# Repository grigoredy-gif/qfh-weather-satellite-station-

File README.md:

# QFH weather-satellite station: my own antenna and an all-discrete receiver

I'm Edy Grigore, an Electrical Engineering student at the University of
Twente. This is my personal project to receive weather satellites on 137 MHz
with hardware I designed myself: a QFH antenna and a superheterodyne receiver
built only from discrete parts (transistors, diodes, coils and capacitors, no
ICs in the signal path).

## Why I'm doing this

In my first year, the Module 4 project was to design an antenna and a
transmitter PCB. I really enjoyed that field, together with the High Frequency
Electronics, Electromagnetostatics and Electrodynamics courses, so I wanted to
go deeper: design my own antenna and my own receiver, and do the receiver fully
analog so I have to understand every stage at component level.

The NOAA satellites the receiver was designed for were switched off in 2025,
and the remaining Meteor-M satellites send a digital signal an analog FM
receiver cannot decode. So I test the antenna and the receiver separately: the
antenna with an SDR on Meteor-M, the receiver with recorded NOAA passes played
back through an ADALM-Pluto. More in the
[receiver README](fm_receiver/README.md#motivation).

## What's in here

| Folder | What it is | Status |
|---|---|---|
| [`qfh_matlab`](qfh_matlab) | MATLAB toolchain that designs the QFH antenna, exports it to NEC2 and prints a drilling template | antenna designed, simulated and built |
| [`fm_receiver`](fm_receiver) | the receiver design and its LTspice simulations, block by block up to the full chain | simulated from RF input to the ADC |
| [`pcb`](pcb) | the KiCad board for the receiver | designed and checked, ready to order |
| [`lrpt_decoder`](lrpt_decoder) | my own MATLAB analysis chain for Meteor-M LRPT recordings | working; taught me my signal was too weak |
| [`baseband_tools`](baseband_tools) | tools to check an SDR recording before decoding it | working |

## Highlights

- A superheterodyne receiver with about **130 dB** of gain: band-pass filter,
  LNA, mixer, a 25 MHz crystal oscillator multiplied ×5 to 125 MHz, a 12.9 MHz
  IF with four cascode stages, a limiter and a slope detector.
- Every block **simulated in LTspice** on its own, then connected, then the
  whole receiver from an FM input to the audio at the ADC.
- A **2-layer PCB** (180 × 75 mm, 196 parts) with the layout built around RF
  rules: an unbroken ground plane, a straight IF strip, tight tuned circuits
  and test points for block-by-block bring-up.
- The antenna toolchain reproduces its reference program **exactly** (all 127
  NEC wire cards identical) and adds a frequency correction found in simulation.

## What's next

Order and build the PCB, align it one block at a time, and feed it a recorded
satellite pass. On the reception side: an LNA and a 137 MHz SAW filter in
front of the SDR, then another try at Meteor-M.

After that, I want to close the loop with my own hardware on both ends: build
a second QFH antenna and an FM transmitter on my own PCB, and send information
between the two stations, on a frequency I'm allowed to transmit on.

## Tools

LTspice, KiCad 10, MATLAB R2025a, 4nec2 / NEC2, SatDump, an ADALM-Pluto SDR
and a miniVNA Tiny.

## Credits and license

This is my project. I used Claude (Anthropic) as an AI assistant along the
way; each folder's README says exactly what it helped with. The antenna code
is a MATLAB port of John Coppens' online QFH calculator and of QFH2nec, both
GPL-licensed, so `qfh_matlab` is GPL-3.0. Everything else is MIT licensed
(see [LICENSE](LICENSE)).

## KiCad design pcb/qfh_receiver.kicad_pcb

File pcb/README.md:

# PCB — discrete 137.9 MHz FM satellite receiver

This is the circuit board for the receiver I simulated in
[`../fm_receiver`](../fm_receiver). The board is built from that simulation:
its schematic was generated from the full-receiver netlist `sim12`, and if the
board and that netlist ever disagree, the netlist wins.

## The board at a glance

| | |
|---|---|
| Size | 180 × 75 mm, 2 layers, FR4 1.6 mm |
| Parts | 196, all on the top side |
| Bottom layer | one ground plane |
| Controller | ESP32-DevKitC V4 on a socket (its ADC digitizes the audio) |
| Supply | the DevKitC's 5V pin (really about 4.6 V), about 41 mA |
| Checks | KiCad DRC clean at a 0.254 mm clearance floor; schematic and board match pad for pad |

## Floorplan

```
+--------------------------------------------------------------------------+
| [SMA ant] BPF (2 air coils, | LNA | MIXER | == IF STRIP, 96 dB, straight |
|  plane cutouts) [SMA test]  | SMD | +T1   |  T2 [1][2][3][4] lim | DET T7 |
|-------- via wall ----------------------------------------------- via wall|
| LO CHAIN: xtal 25MHz | buffer | x5 (2 air coils) -> up into mixer LO port |
|                      AUDIO chain (2400 Hz, folds freely) <- from detector |
|  power entry / bulk filter          ESP32 module socket [USB over edge] > |
+--------------------------------------------------------------------------+
```

The weakest signals (microvolts) start at the left edge and the strongest
(volts) end at the right. The IF strip runs in a straight line with its input
and output at opposite ends, because with 96 dB of gain even a little coupling
from the output back to the input would make it oscillate.

## Layout rules I followed

- **The bottom layer is ground.** Everything is routed on top. A few short
  bottom-layer hops were unavoidable where a trace had to cross another; each
  one is listed and justified in the design log.
- **Shielding provisions for free.** Rows of ground vias between the IF stages
  and between the RF and the LO/audio sections, with exposed ground strips so a
  brass shield can be soldered on later if the strip oscillates.
- **Tight RF loops.** Every tuned circuit's parts sit right at its coil, and the
  LNA's emitter bypass is within about 5 mm of copper of the transistor. At VHF
  a few nanohenries of track change the tuning and the gain.
- **A real 50 ohm antenna input.** The SMA feeds the filter through a 1.5 mm
  coplanar line with ground on both sides.
- **Decoupling everywhere.** Every IF stage has its own 100 nF capacitors on its
  supply and on its cascode bias, fed through its own 10 ohm resistor, so the
  stages cannot talk to each other through the supply.
- **Test points for bring-up.** A second, unfitted SMA with a 0 ohm link at the
  filter→LNA seam (to measure the filter and the LNA separately on a VNA), an
  injection pad at the first IF stage, and a monitor pad on the audio.
- **No parts on the back and no mounting holes**, both on purpose.

The toroids (T37-6, 27 turns) and the air coils (5 mm diameter) use my own
footprints in `qfh_receiver.pretty`. The air-coil footprint keeps copper away
from under the coil, because a ground plane there would kill its Q.

## How I checked it

KiCad's design-rule check is clean at a 0.254 mm clearance floor. The
schematic was generated from the simulation netlist and compared with the board
pad by pad (418 connections, no differences). Every part value was checked
against a real catalogue part at Farnell. I also had the board reviewed by
independent AI review passes, which is how several of the issues below were
found.

## Issues found and fixed

- **Two TO-92 transistor types had base and emitter swapped** because a
  generic symbol used the wrong pin order. Lesson: check each footprint's pinout
  against the datasheet, not against the symbol library.
- **The ESP32 socket would not have powered anything.** The 5 V feed landed on
  a GPIO pin and the enable pin was grounded. I fixed it after checking the
  DevKitC pinout from several sources and every way the module could be
  plugged in.
- **The "5 V" supply is really 4.6 V**, because the DevKitC puts a Schottky
  diode after USB. I re-centred every bias divider in the simulation for 4.6 V
  instead of accepting lower gain.
- **Some specified trimmers did not exist as real parts.** Together with the
  board's own parasitics this pushed three tuned circuits to the end of their
  trimmer range. I re-split the fixed capacitor and the trimmer in each one so
  the trimmer now lands mid-range.
- **The LNA's emitter bypass capacitor was 20 mm from the transistor.** That
  is about 12 nH, which would have cost 4–5 dB of gain. It is now within 5 mm.

## Bring-up plan

1. Power only: check every DC voltage against `sim12`.
2. Local oscillator: 25 MHz at the crystal, then 125 MHz at the mixer.
3. Filter and LNA: fit the test SMA, remove the 0 ohm link, sweep them on the
   VNA. Expect about 39 dB of image rejection and an LNA gain of at least
   13.5 dB.
4. IF strip: with no signal, the limiter output should show only noise (a
   steady tone means it oscillates). Then inject 12.9 MHz at the test pad and
   align the tanks.
5. The whole chain: a recorded APT pass from the Pluto into the antenna input.

Expected trimmer settings: band-pass filter about 6.5 pF, ×5 multiplier about
5.4 pF, LO output about 5.8 pF. If one lands far from that, its coil probably
came out wrong.

## Ordering

The bill of materials with Farnell order codes is `fabrication/qfh_receiver_bom.csv`, and the gerbers for JLCPCB are `fabrication/qfh_receiver_gerbers_jlc.zip`.
Every pF-range capacitor must be NP0/C0G, and the crystal must be a
fundamental-mode part. Both SMAs are edge-launch parts whose pads run to the
board edge on purpose, so the board house may ask about copper at the edge.

## Files

| File | What it is |
|---|---|
| `qfh_receiver.kicad_pro` / `.kicad_sch` / `.kicad_pcb` | the KiCad project, schematic and board |
| `qfh_receiver.kicad_dru` | custom design rules (edge clearance at the two SMAs) |
| `qfh_receiver.pretty/` | my footprints for the toroids and air coils |
| `fabrication/` | the bill of materials and the gerbers for ordering |
| `img/` | board renders |
| [`DESIGN_LOG.md`](DESIGN_LOG.md) | the complete step-by-step design log |

## Attribution

This board is my project: I set the requirements and the layout rules, and I
approved every change. I will assemble, align and measure it myself. I used
Claude (Anthropic) as an AI assistant for the KiCad work: following my
requirements and reviews, it did most of the placement and routing by script,
ran the design checks and did independent review passes. The full step-by-step
record is in [`DESIGN_LOG.md`](DESIGN_LOG.md). The motivation for the project is
in the [receiver README](../fm_receiver/README.md).

Edy Grigore

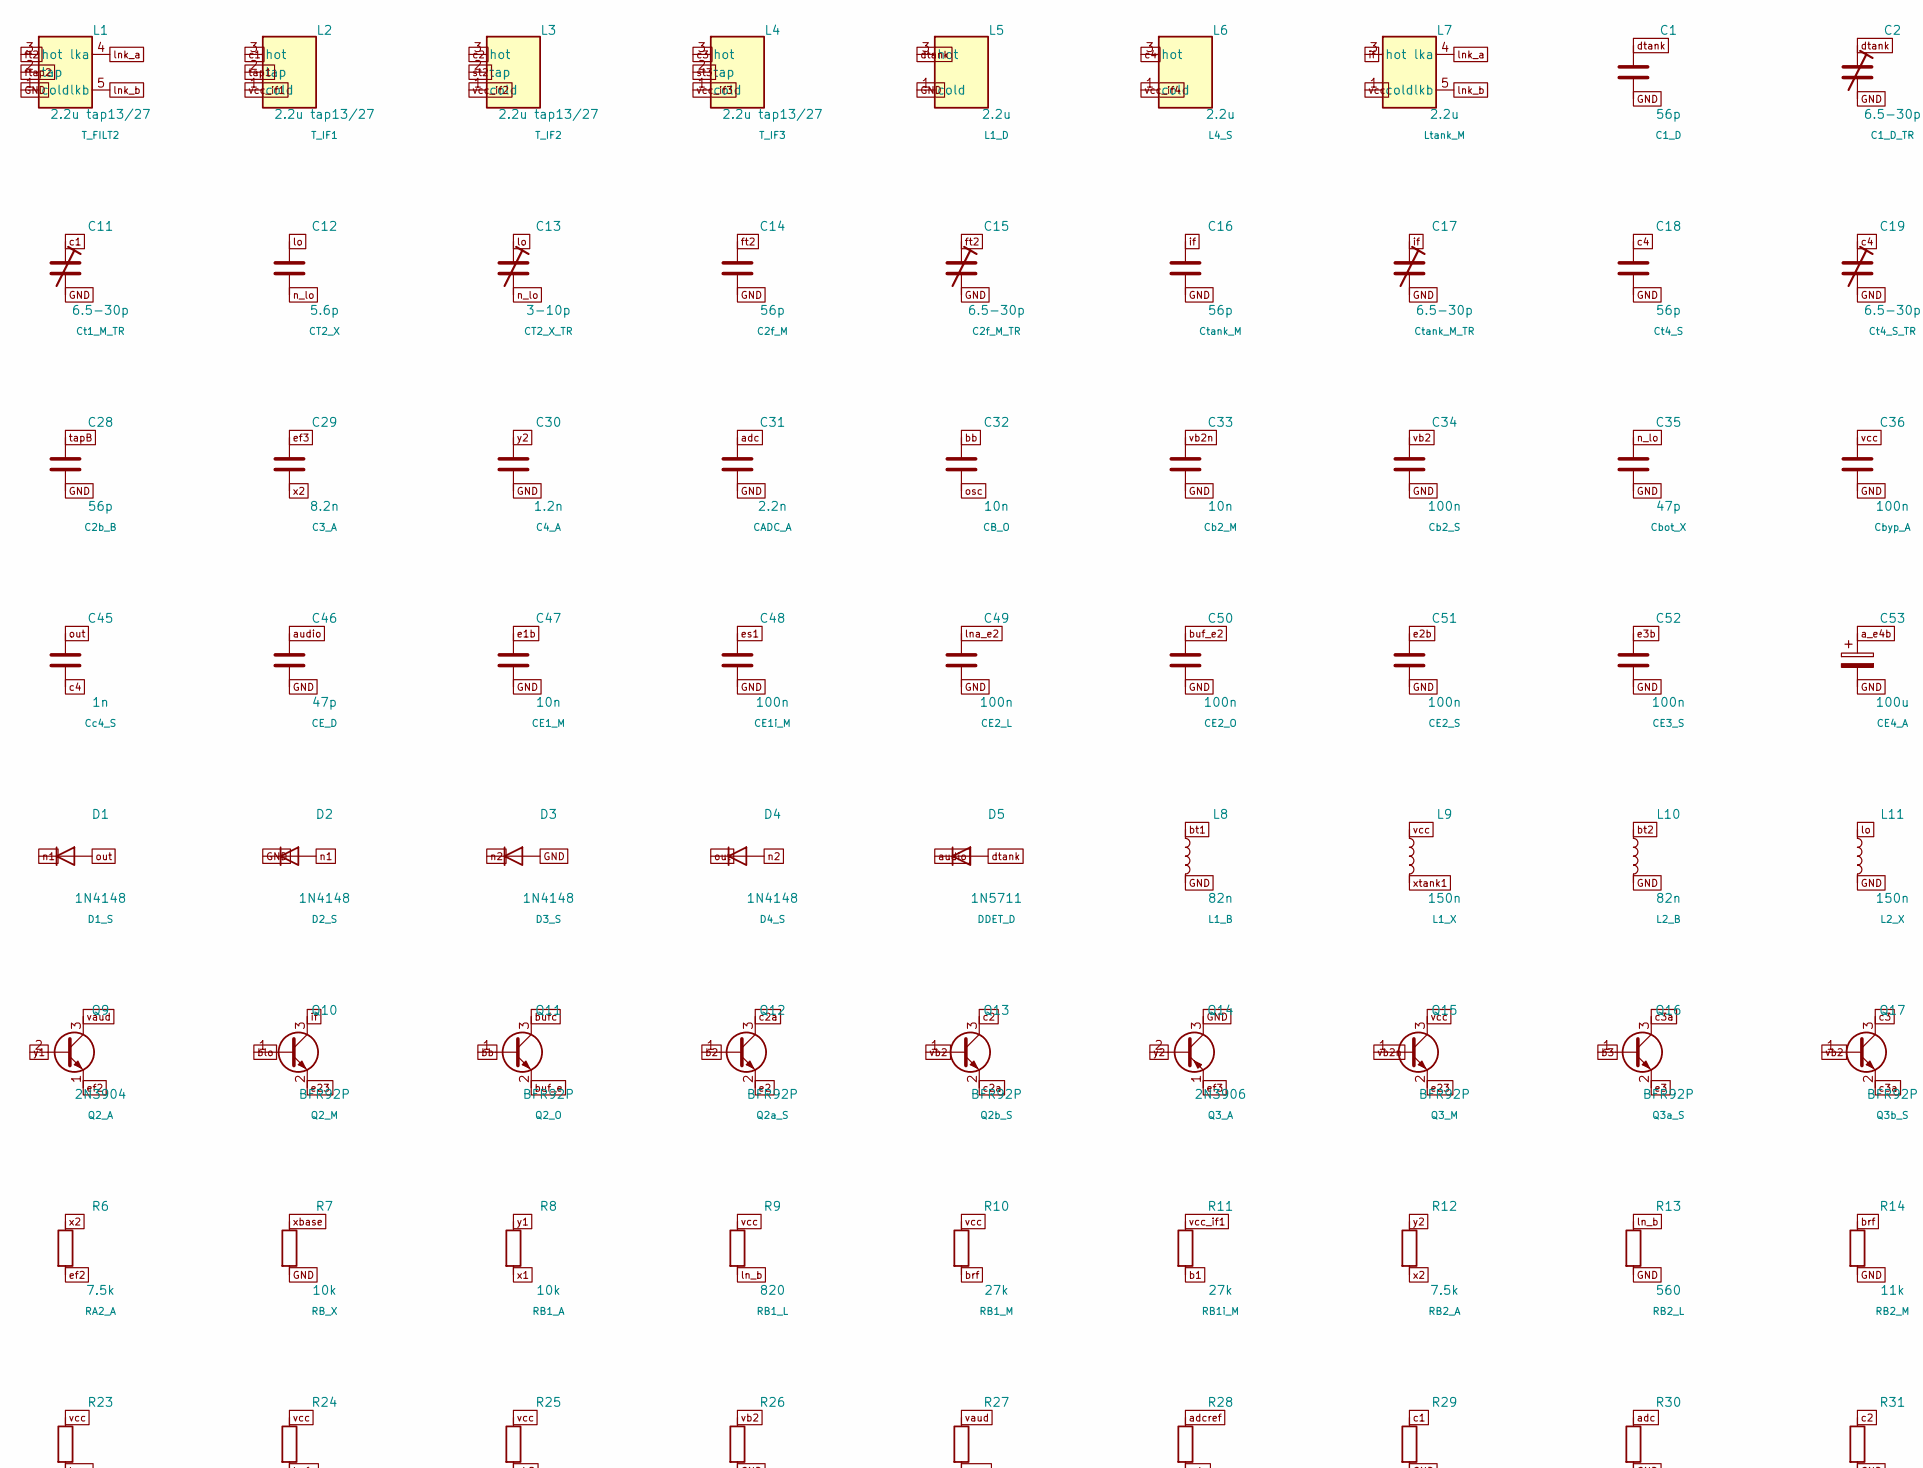
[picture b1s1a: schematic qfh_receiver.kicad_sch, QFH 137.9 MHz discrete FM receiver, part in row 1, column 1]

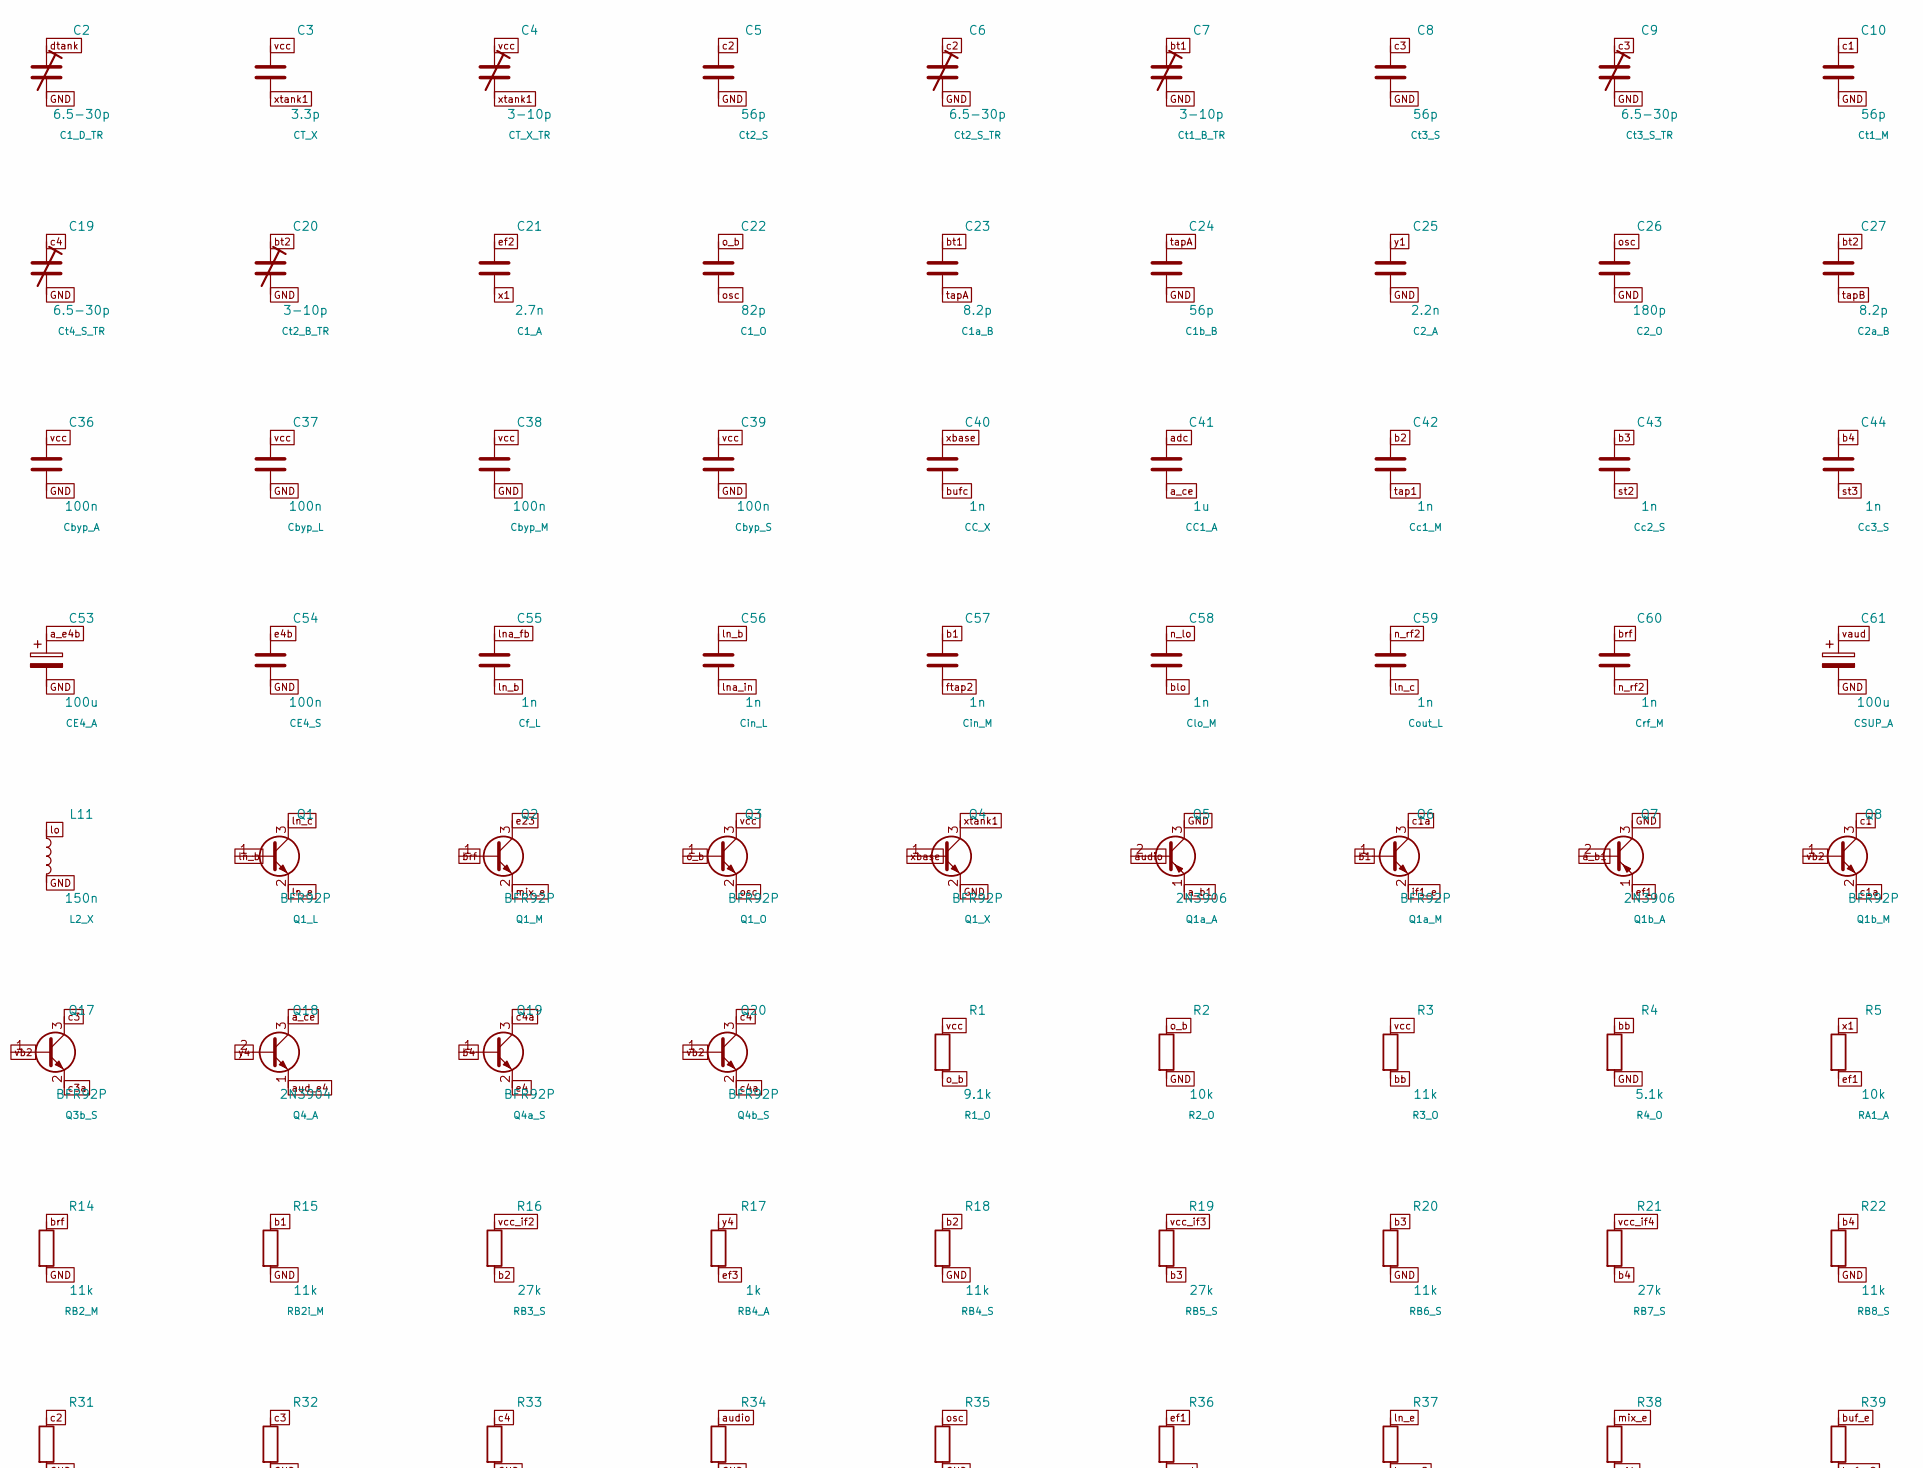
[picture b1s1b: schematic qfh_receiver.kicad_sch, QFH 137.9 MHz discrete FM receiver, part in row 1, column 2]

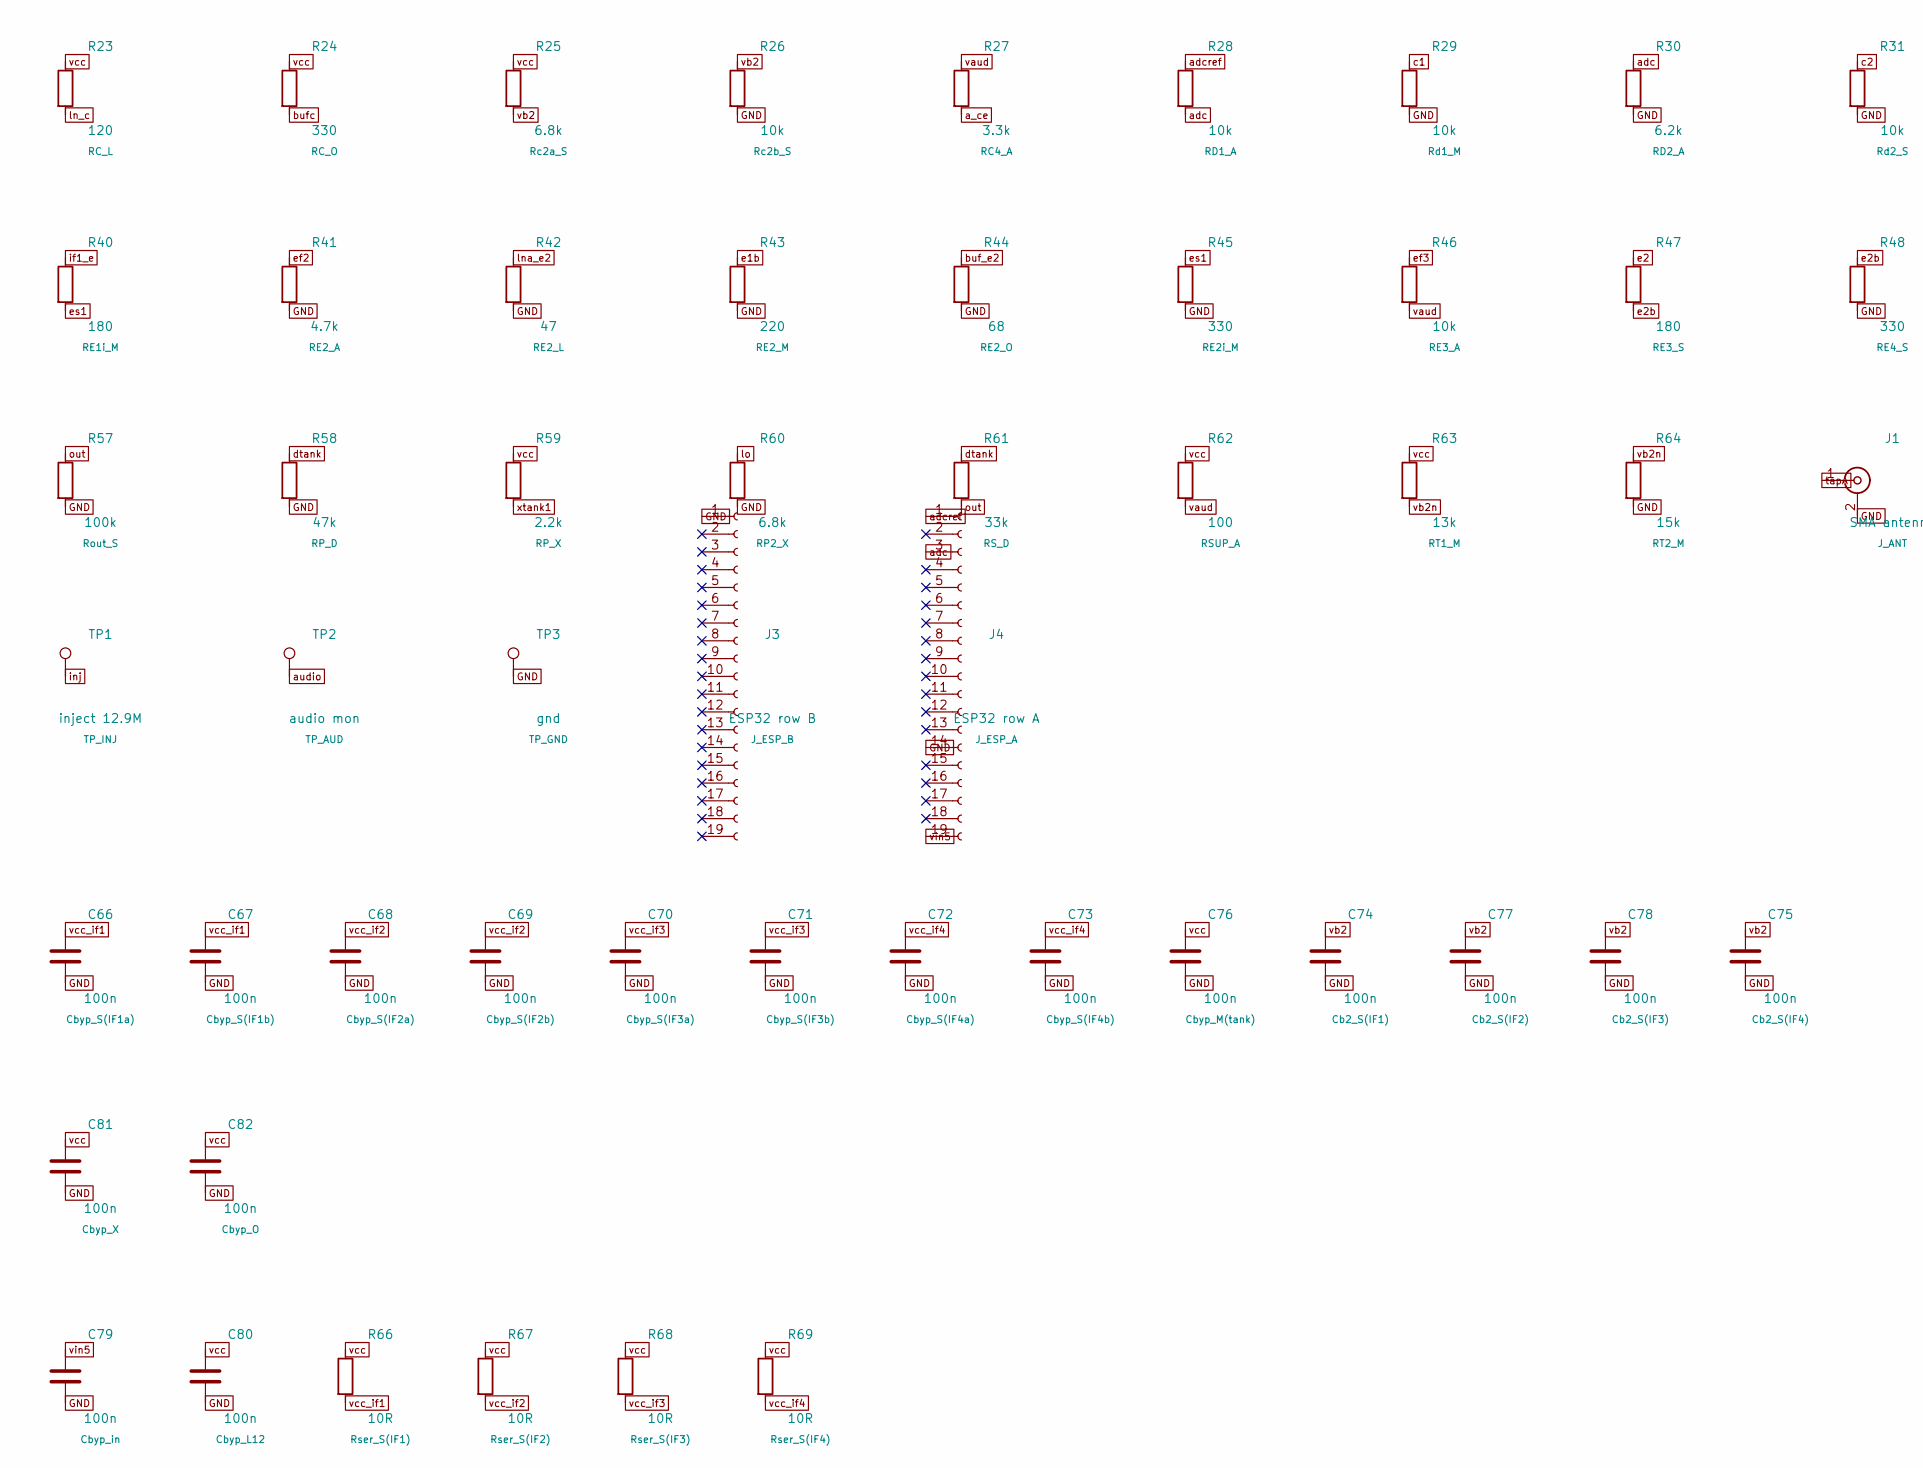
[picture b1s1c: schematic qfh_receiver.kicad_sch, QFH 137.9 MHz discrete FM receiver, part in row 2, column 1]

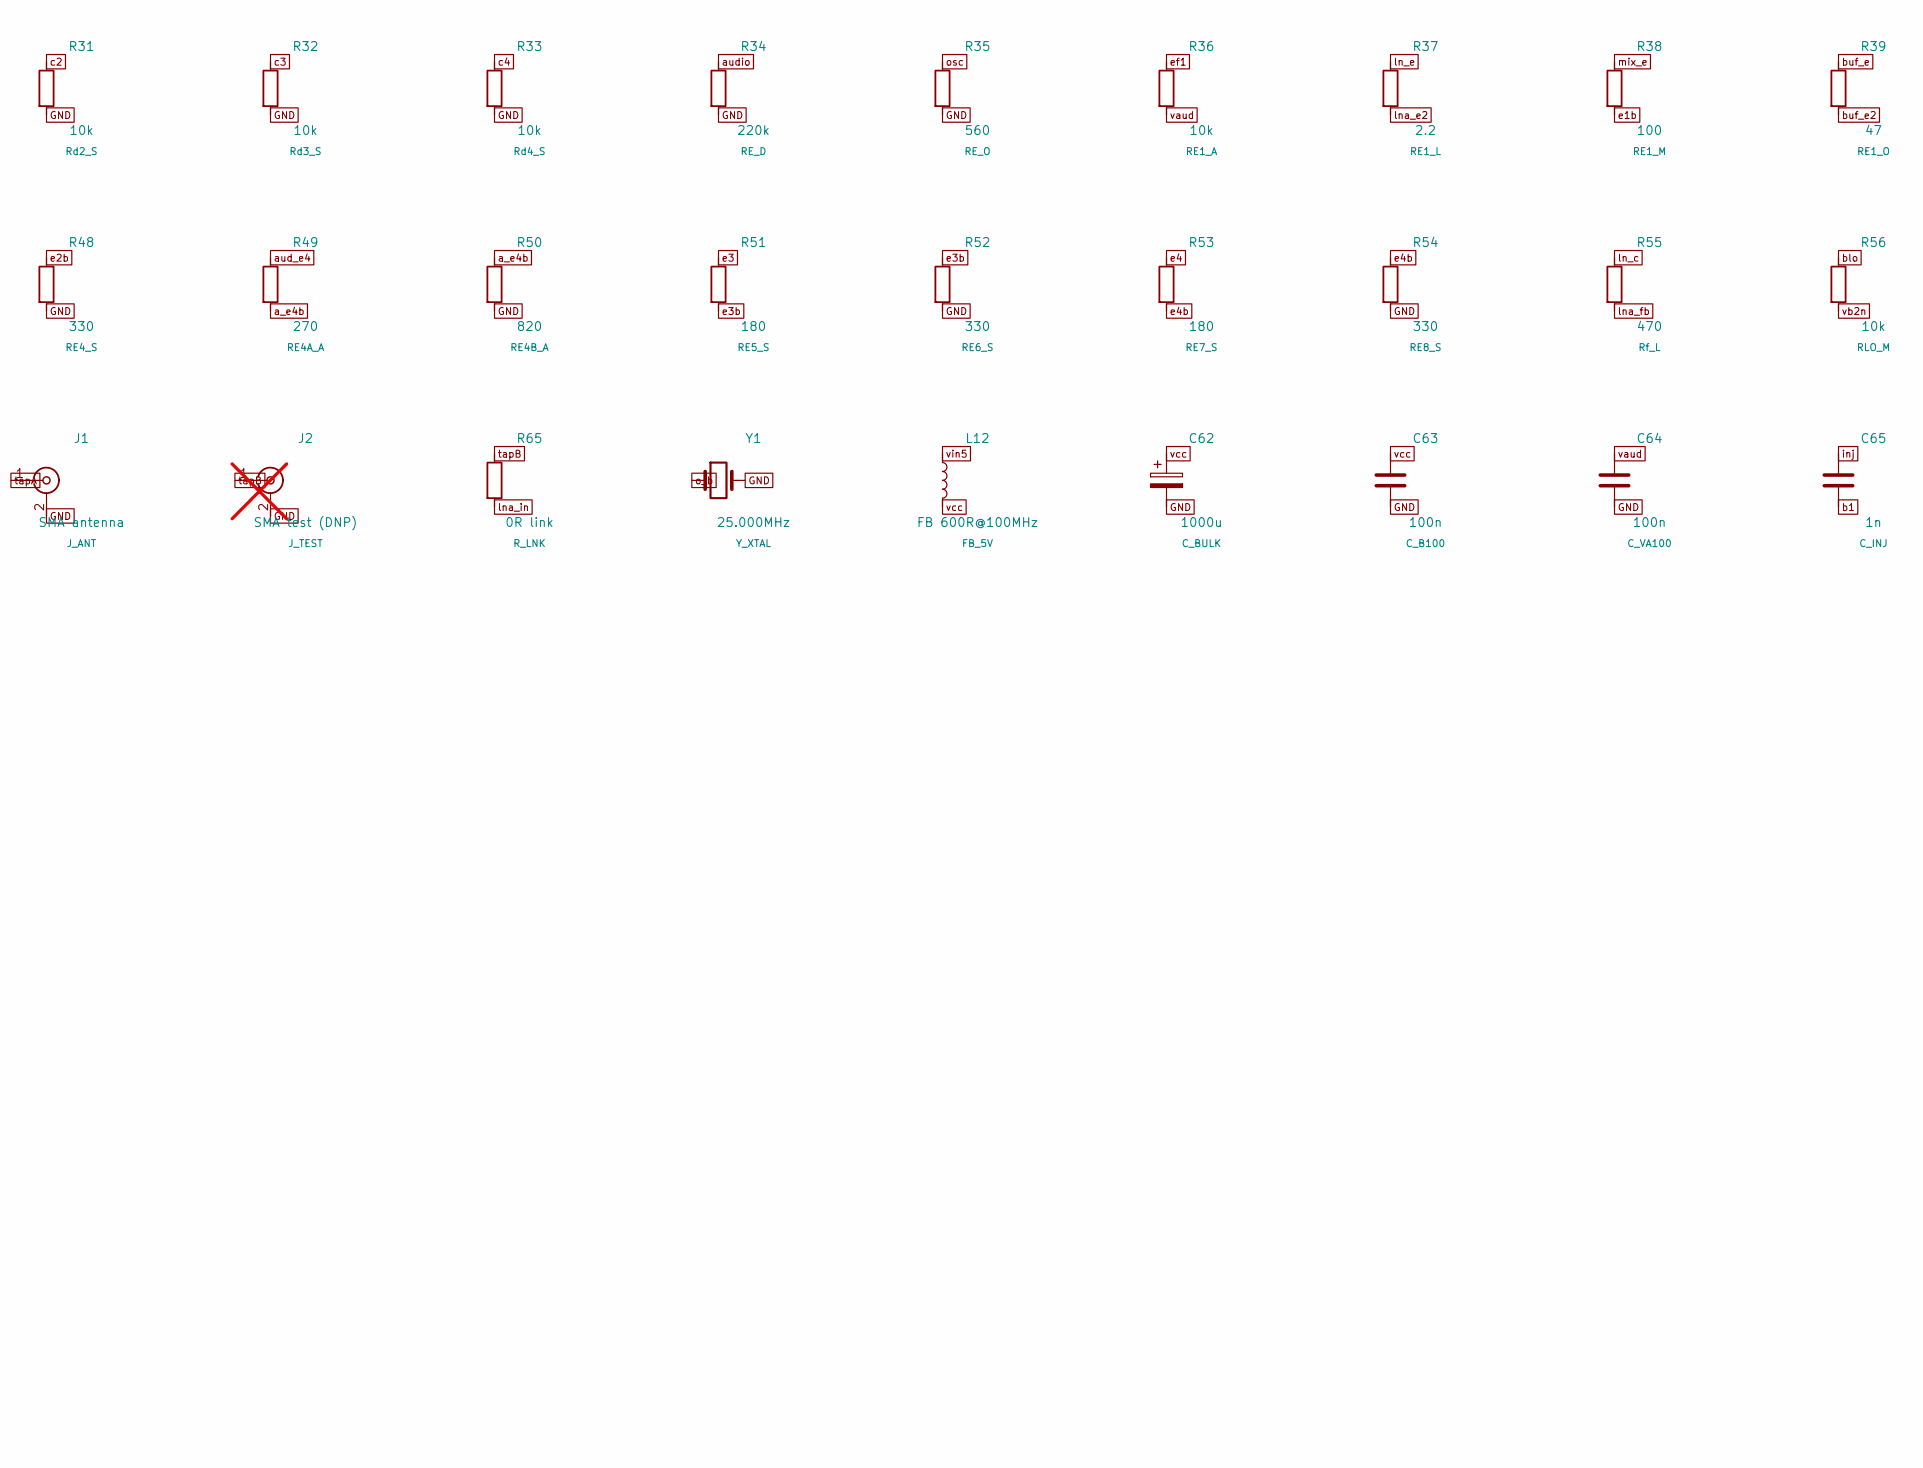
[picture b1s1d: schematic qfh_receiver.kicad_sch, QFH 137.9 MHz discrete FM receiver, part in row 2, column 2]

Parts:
C1, C5, C8, C10, C14, C16, C18, C24, C28: 56p; C_0805_2012Metric
C2, C6, C9, C11, C15, C17, C19: 6.5-30p; C_Trimmer_Murata_TZC3; MPN TZC3P300A110R00; Farnell 2456139
C3: 3.3p; C_0805_2012Metric
C4, C7, C13, C20: 3-10p; C_Trimmer_Murata_TZC3; MPN TZC3R100A110R00; Farnell 2456140RL
C12: 5.6p; C_0805_2012Metric
C21: 2.7n; C_0805_2012Metric
C22: 82p; C_0805_2012Metric
C23, C27: 8.2p; C_0805_2012Metric
C25, C31: 2.2n; C_0805_2012Metric
C26: 180p; C_0805_2012Metric
C29: 8.2n; C_0805_2012Metric
C30: 1.2n; C_0805_2012Metric
C32, C33, C47: 10n; C_0805_2012Metric
C34, C36, C37, C38, C39, C48, C49, C50, C51, C52, C54, C63, C64, C66, C67, C68, C69, C70, C71, C72, C73, C74, C75, C76, C77, C78, C79, C80, C81, C82: 100n; C_0805_2012Metric
C35, C46: 47p; C_0805_2012Metric
C40, C42, C43, C44, C45, C55, C56, C57, C58, C59, C60, C65: 1n; C_0805_2012Metric
C41: 1u; C_0805_2012Metric
C53, C61: 100u; CP_Radial_D5.0mm_P2.50mm
C62: 1000u; CP_Radial_D8.0mm_P3.50mm
D1, D2, D3, D4: 1N4148; D_DO-35_SOD27_P2.54mm_Vertical_AnodeUp
D5: 1N5711; D_DO-35_SOD27_P2.54mm_Vertical_AnodeUp
J1: SMA antenna; SMA_Amphenol_132289_EdgeMount; MPN 132289; Farnell 2112467
J2: SMA test (DNP); SMA_Amphenol_132289_EdgeMount; MPN 132289; Farnell 2112467; not fitted
J3: ESP32 row B; PinSocket_1x19_P2.54mm_Vertical
J4: ESP32 row A; PinSocket_1x19_P2.54mm_Vertical
L1, L2, L3, L4: 2.2u tap13/27; TOROID_T37-6_UNIVERSAL
L5, L6, L7: 2.2u; TOROID_T37-6_UNIVERSAL
L8, L10: 82n; AIRCOIL_5MM
L9, L11: 150n; AIRCOIL_5MM
L12: FB 600R@100MHz; L_0805_2012Metric
Q1, Q2, Q3, Q4, Q6, Q8, Q10, Q11, Q12, Q13, Q15, Q16, Q17, Q19, Q20: BFR92P; SOT-23; MPN BFR92PE6327HTSA1
Q5, Q7, Q14: 2N3906; TO-92_Inline_Wide
Q9, Q18: 2N3904; TO-92_Inline_Wide
R1: 9.1k; R_0805_2012Metric
R2, R5, R7, R8, R26, R28, R29, R31, R32, R33, R36, R46, R56: 10k; R_0805_2012Metric
R3, R14, R15, R18, R20, R22: 11k; R_0805_2012Metric
R4: 5.1k; R_0805_2012Metric
R6, R12: 7.5k; R_0805_2012Metric
R9, R50: 820; R_0805_2012Metric
R10, R11, R16, R19, R21: 27k; R_0805_2012Metric
R13, R35: 560; R_0805_2012Metric
R17: 1k; R_0805_2012Metric
R23: 120; R_0805_2012Metric
R24, R45, R48, R52, R54: 330; R_0805_2012Metric
R25, R60: 6.8k; R_0805_2012Metric
R27: 3.3k; R_0805_2012Metric
R30: 6.2k; R_0805_2012Metric
R34: 220k; R_0805_2012Metric
R37: 2.2; R_0805_2012Metric
R38, R62: 100; R_0805_2012Metric
R39, R42: 47; R_0805_2012Metric
R40, R47, R51, R53: 180; R_0805_2012Metric
R41: 4.7k; R_0805_2012Metric
R43: 220; R_0805_2012Metric
R44: 68; R_0805_2012Metric
R49: 270; R_0805_2012Metric
R55: 470; R_0805_2012Metric
R57: 100k; R_0805_2012Metric
R58: 47k; R_0805_2012Metric
R59: 2.2k; R_0805_2012Metric
R61: 33k; R_0805_2012Metric
R63: 13k; R_0805_2012Metric
R64: 15k; R_0805_2012Metric
R65: 0R link; R_0805_2012Metric
R66, R67, R68, R69: 10R; R_0805_2012Metric
TP1: inject 12.9M; TestPoint_Pad_D2.0mm
TP2: audio mon; TestPoint_Pad_D2.0mm
TP3: gnd; TestPoint_Pad_D2.0mm
Y1: 25.000MHz; Crystal_HC49-4H_Vertical

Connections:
GND: C1.2, C2.2, C5.2, C6.2, C7.2, C8.2, C9.2, C10.2, C11.2, C14.2, C15.2, C16.2, C17.2, C18.2, C19.2, C20.2, C24.2, C25.2, C26.2, C28.2, C30.2, C31.2, C33.2, C34.2, C35.2, C36.2, C37.2, C38.2, C39.2, C46.2, C47.2, C48.2, C49.2, C50.2, C51.2, C52.2, C53.2, C54.2, C61.2, C62.2, C63.2, C64.2, C66.2, C67.2, C68.2, C69.2, C70.2, C71.2, C72.2, C73.2, C74.2, C75.2, C76.2, C77.2, C78.2, C79.2, C80.2, C81.2, C82.2, D2.1 (K), D3.2 (A), J1.2 (Ext), J2.2 (Ext), J3.1 (Pin_1_1), J4.14, L1.1 (cold), L5.1 (cold), L8.2, L10.2, L11.2, Q4.2 (E), Q5.3 (C), Q7.3 (C), Q14.3 (C), R2.2, R4.2, R7.2, R13.2, R14.2, R15.2, R18.2, R20.2, R22.2, R26.2, R29.2, R30.2, R31.2, R32.2, R33.2, R34.2, R35.2, R41.2, R42.2, R43.2, R44.2, R45.2, R48.2, R50.2, R52.2, R54.2, R57.2, R58.2, R60.2, R64.2, TP3.1 (1_1), Y1.2
a_b1: Q5.1 (E), Q7.2 (B)
a_ce: C41.2, Q18.3 (C), R27.2
a_e4b: C53.1, R49.2, R50.1
adc: C31.1, C41.1, J4.3, R28.2, R30.1
adcref: J4.1, R28.1
aud_e4: Q18.1 (E), R49.1
audio: C46.1, D5.1 (K), Q5.2 (B), R34.1, TP2.1 (1_1)
b1: C57.1, C65.2, Q6.1 (B), R11.2, R15.1
b2: C42.1, Q12.1 (B), R16.2, R18.1
b3: C43.1, Q16.1 (B), R19.2, R20.1
b4: C44.1, Q19.1 (B), R21.2, R22.1
bb: C32.1, Q11.1 (B), R3.2, R4.1
blo: C58.2, Q10.1 (B), R56.1
brf: C60.1, Q2.1 (B), R10.2, R14.1
bt1: C7.1, C23.1, L8.1
bt2: C20.1, C27.1, L10.1
buf_e: Q11.2 (E), R39.1
buf_e2: C50.1, R39.2, R44.1
bufc: C40.2, Q11.3 (C), R24.2
c1: C10.1, C11.1, L2.3 (hot), Q8.3 (C), R29.1
c1a: Q6.3 (C), Q8.2 (E)
c2: C5.1, C6.1, L3.3 (hot), Q13.3 (C), R31.1
c2a: Q12.3 (C), Q13.2 (E)
c3: C8.1, C9.1, L4.3 (hot), Q17.3 (C), R32.1
c3a: Q16.3 (C), Q17.2 (E)
c4: C18.1, C19.1, C45.2, L6.3 (hot), Q20.3 (C), R33.1
c4a: Q19.3 (C), Q20.2 (E)
dtank: C1.1, C2.1, D5.2 (A), L5.3 (hot), R58.1, R61.1
e1b: C47.1, R38.2, R43.1
e2: Q12.2 (E), R47.1
e2b: C51.1, R47.2, R48.1
e3: Q16.2 (E), R51.1
e3b: C52.1, R51.2, R52.1
e4: Q19.2 (E), R53.1
e4b: C54.1, R53.2, R54.1
e23: Q2.3 (C), Q10.2 (E), Q15.2 (E)
ef1: Q7.1 (E), R5.2, R36.1
ef2: C21.1, Q9.1 (E), R6.2, R41.1
ef3: C29.1, Q14.1 (E), R17.2, R46.1
es1: C48.1, R40.2, R45.1
ft2: C14.1, C15.1, L1.3 (hot)
ftap2: C57.2, L1.2 (tap)
if: C16.1, C17.1, L7.3 (hot), Q10.3 (C)
if1_e: Q6.2 (E), R40.1
inj: C65.1, TP1.1 (1_1)
ln_b: C55.2, C56.1, Q1.1 (B), R9.2, R13.1
ln_c: C59.2, Q1.3 (C), R23.2, R55.1
ln_e: Q1.2 (E), R37.1
lna_e2: C49.1, R37.2, R42.1
lna_fb: C55.1, R55.2
lna_in: C56.2, R65.2
lnk_a: L1.4 (lka), L7.4 (lka)
lnk_b: L1.5 (lkb), L7.5 (lkb)
lo: C12.1, C13.1, L11.1, R60.1
mix_e: Q2.2 (E), R38.1
n1: D1.1 (K), D2.2 (A)
n2: D3.1 (K), D4.2 (A)
n_lo: C12.2, C13.2, C35.1, C58.1
n_rf2: C59.1, C60.2
o_b: C22.1, Q3.1 (B), R1.2, R2.1, Y1.1
osc: C22.2, C26.1, C32.2, Q3.2 (E), R35.1
out: C45.1, D1.2 (A), D4.1 (K), R57.1, R61.2
st2: C43.2, L3.2 (tap)
st3: C44.2, L4.2 (tap)
tap1: C42.2, L2.2 (tap)
tapA: C23.2, C24.1, J1.1 (In)
tapB: C27.2, C28.1, J2.1 (In), R65.1
vaud: C61.1, C64.1, Q9.3 (C), R27.1, R36.2, R46.2, R62.2
vb2: C34.1, C74.1, C75.1, C77.1, C78.1, Q8.1 (B), Q13.1 (B), Q17.1 (B), Q20.1 (B), R25.2, R26.1
vb2n: C33.1, Q15.1 (B), R56.2, R63.2, R64.1
vcc: C3.1, C4.1, C36.1, C37.1, C38.1, C39.1, C62.1, C63.1, C76.1, C80.1, C81.1, C82.1, L7.1 (cold), L9.1, L12.2, Q3.3 (C), Q15.3 (C), R1.1, R3.1, R9.1, R10.1, R23.1, R24.1, R25.1, R59.1, R62.1, R63.1, R66.1, R67.1, R68.1, R69.1
vcc_if1: C66.1, C67.1, L2.1 (cold), R11.1, R66.2
vcc_if2: C68.1, C69.1, L3.1 (cold), R16.1, R67.2
vcc_if3: C70.1, C71.1, L4.1 (cold), R19.1, R68.2
vcc_if4: C72.1, C73.1, L6.1 (cold), R21.1, R69.2
vin5: C79.1, J4.19, L12.1
x1: C21.2, R5.1, R8.2
x2: C29.2, R6.1, R12.2
xbase: C40.1, Q4.1 (B), R7.1
xtank1: C3.2, C4.2, L9.2, Q4.3 (C), R59.2
y1: C25.1, Q9.2 (B), R8.1
y2: C30.1, Q14.2 (B), R12.1
y4: Q18.2 (B), R17.1
